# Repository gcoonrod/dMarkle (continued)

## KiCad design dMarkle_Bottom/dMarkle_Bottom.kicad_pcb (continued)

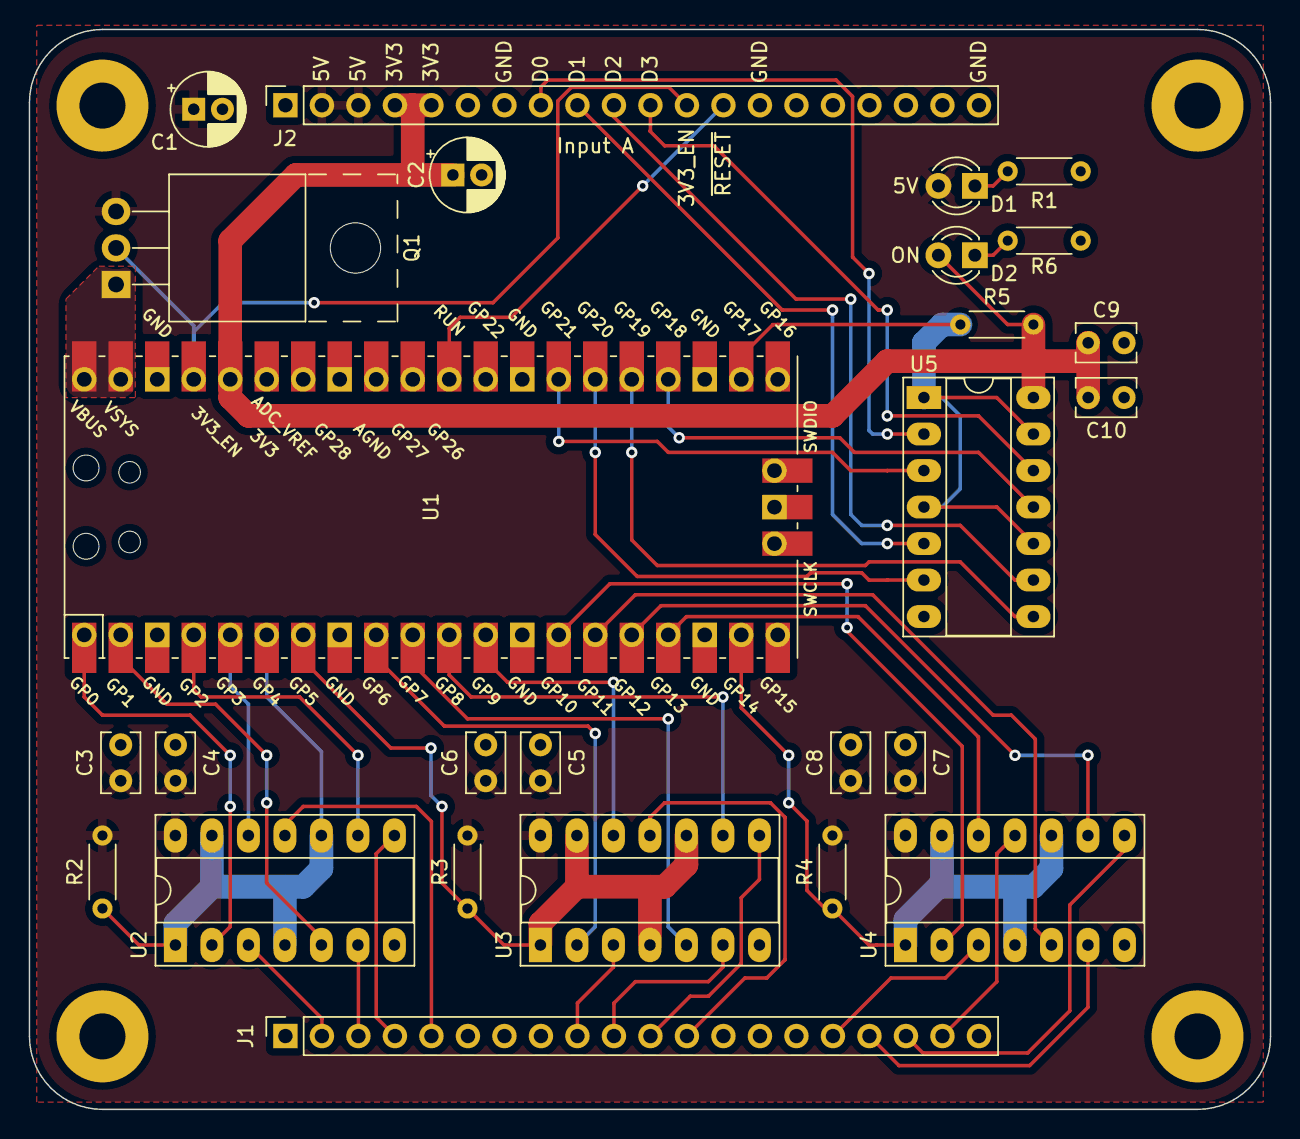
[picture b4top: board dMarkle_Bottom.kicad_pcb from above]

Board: 2 copper layers, 86.4 x 75.1 mm, 30 parts (0 on the bottom side), 44 nets.

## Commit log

2023-01-13 Rev 0 complete
2023-01-13 Add readme
2023-01-18 add placeholder for pico code
2023-01-18 Add another LS125 for rotary encoder output.
2023-01-19 Begin splitting design into top and bottom boards.
2023-01-19 Update library pathing.
2023-01-23 Initial split of dMarkle board
2023-01-23 WIP pico software
2023-01-24 Rev 0.1
2023-01-25 Fixed GPIO pin numbering. Counter working.
2023-01-25 basic version of dice roller working on breadboard
2023-01-25 All 5V usage removed. Rev0.1 complete.
2023-01-25 Remove board split as not needed.
2023-01-25 Clean up schematic and generate output for rev 0.1
2023-01-25 Remove old seg test file
2023-01-25 Readme updates and minor silkscreen changes.
2023-02-01 Board and parts ordered.
2023-02-15 Restructure code layout
2023-02-15 Initial port of TM16xx lib to python.
2023-04-06 Rev 1.1 board top
